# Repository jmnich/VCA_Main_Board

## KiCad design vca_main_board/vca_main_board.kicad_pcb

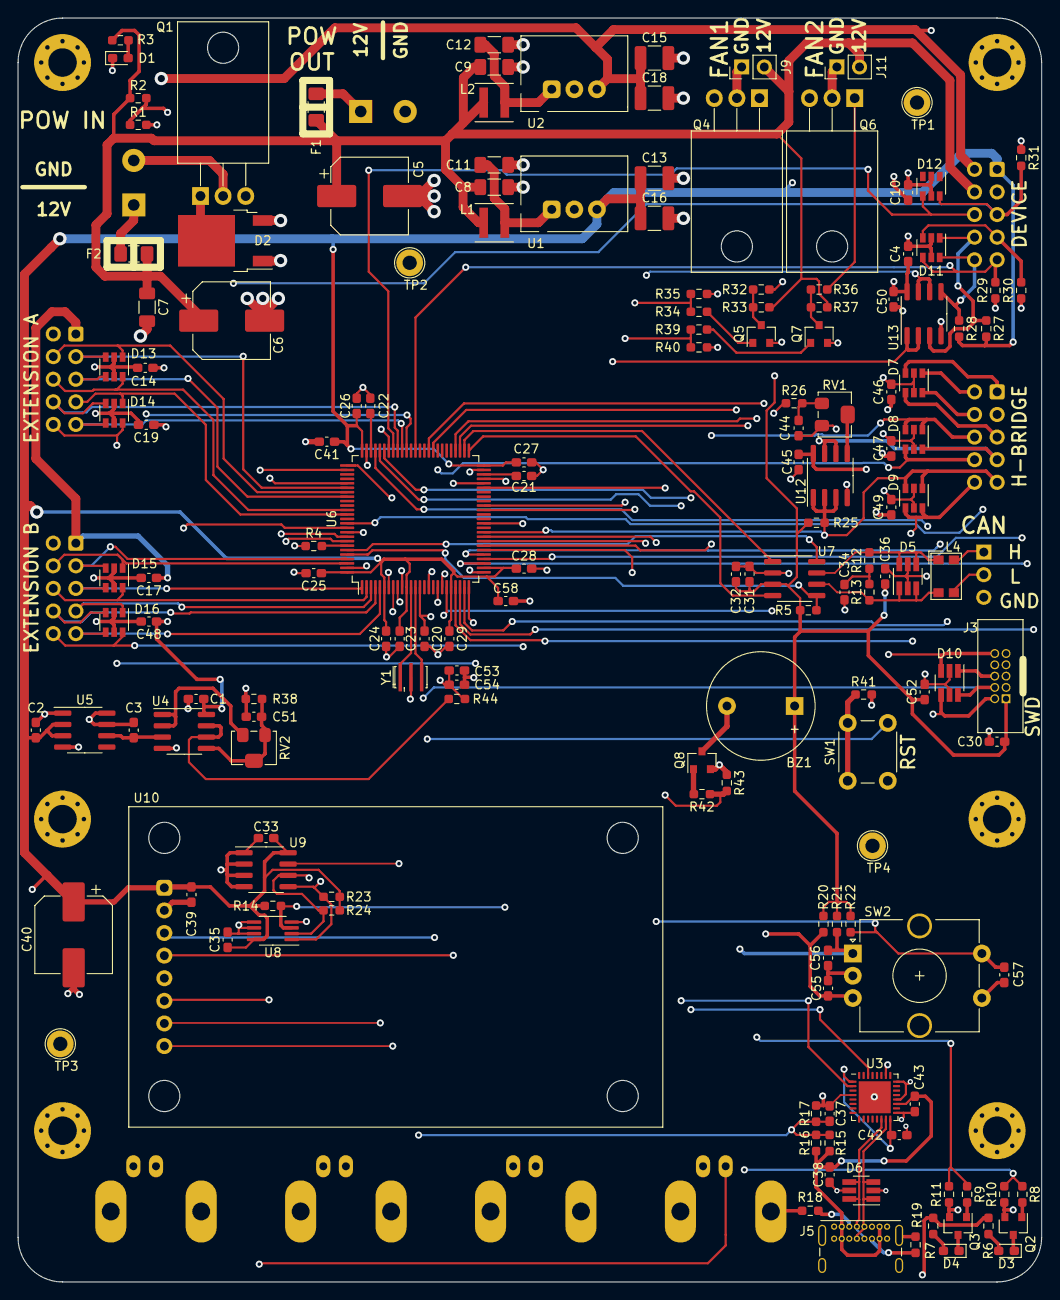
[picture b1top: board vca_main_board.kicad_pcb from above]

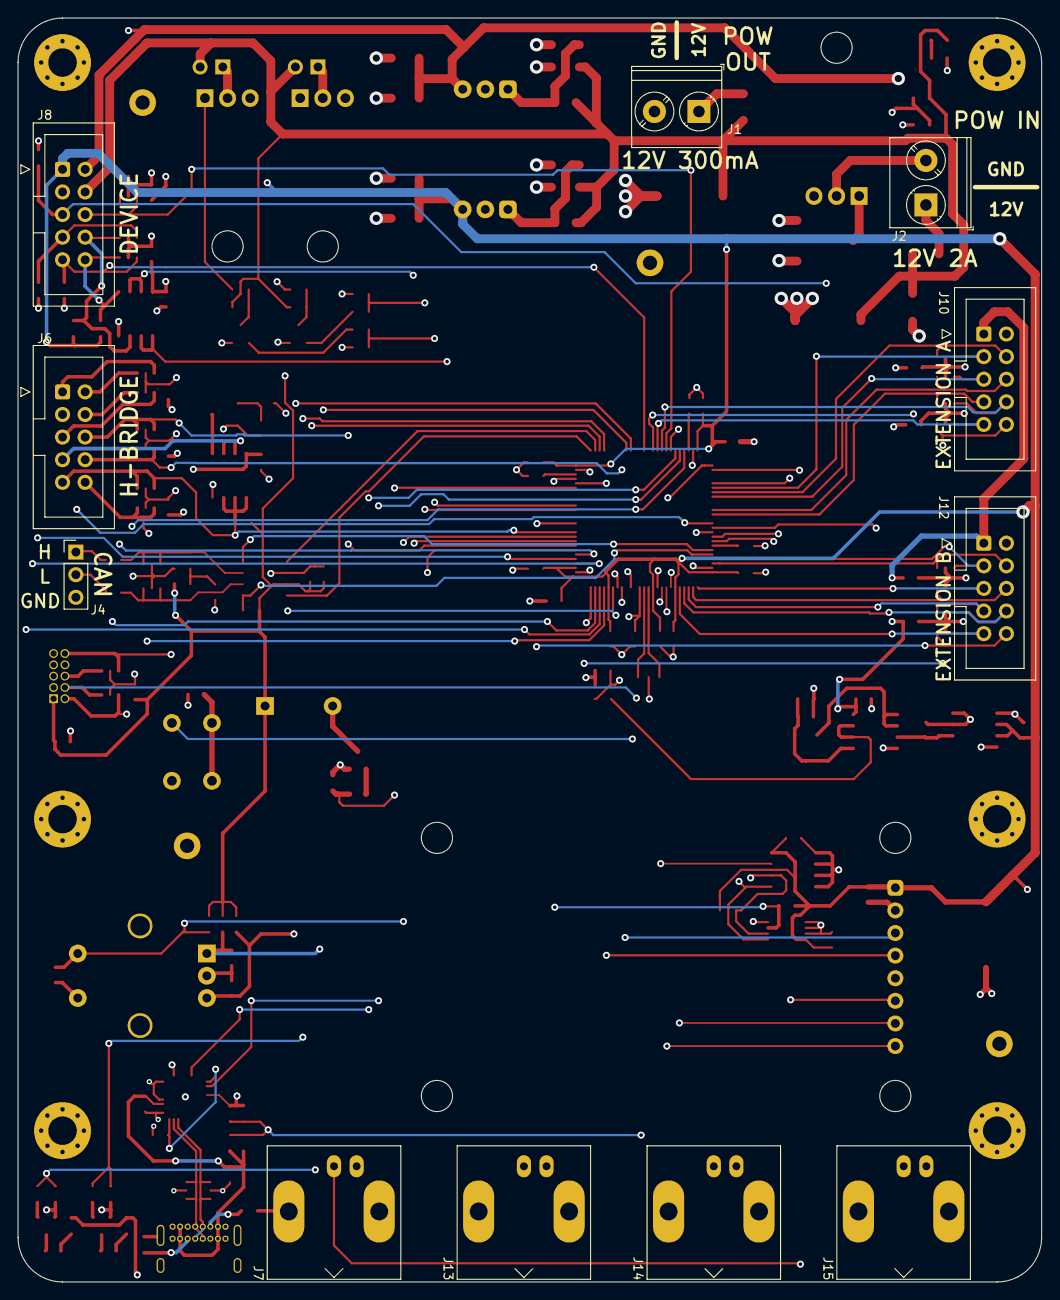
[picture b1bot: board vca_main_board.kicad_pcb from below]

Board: 4 copper layers, 115.0 x 142.0 mm, 174 parts (11 on the bottom side), 115 nets.

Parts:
BZ1: Buzzer; Buzzer_12x9.5RM7.6
C1: 1u 10V; C_0603_1608Metric_Pad1.08x0.95mm_HandSolder
C2, C3, C30, C32, C36, C39, C42, C43, C53: 1u 6.3V; C_0603_1608Metric_Pad1.08x0.95mm_HandSolder
C4, C10, C14, C17, C19, C37, C45, C46, C47, C48, C49, C50: 100n 10V; C_0603_1608Metric_Pad1.08x0.95mm_HandSolder
C5, C6, C40: 180u 50V; CP_Elec_8x10.5
C7, C8, C9, C11, C12: 10u 20V; C_1206_3216Metric_Pad1.33x1.80mm_HandSolder
C13, C15, C16, C18: 22u 10V; C_1210_3225Metric_Pad1.33x2.70mm_HandSolder
C20, C23, C24, C25, C26, C27, C28, C29, C31, C33, C35, C38, C44, C51, C52, C54, C55, C56, C57: 100n 6.3V; C_0603_1608Metric_Pad1.08x0.95mm_HandSolder
C21, C22: 2u2 6.3V; C_0603_1608Metric_Pad1.08x0.95mm_HandSolder
C34: 4n7 10V; C_0603_1608Metric_Pad1.08x0.95mm_HandSolder
C41, C58: 4.7u 6.3V; C_0603_1608Metric_Pad1.08x0.95mm_HandSolder
D1, D3, D4: LED GREEN; LED_0603_1608Metric_Pad1.05x0.95mm_HandSolder
D2: 10A 60V; TO-252-2
D5, D6, D10: ESDA6V1BC6; SOT-23-6_Handsoldering
D7, D8, D9, D11, D12, D13, D14, D15, D16: ESDA6V1BC6; SOT-23-6
F1: Fuse 500mA; Fuse_1206_3216Metric_Pad1.42x1.75mm_HandSolder
F2: Fuse 1A; Fuse_1206_3216Metric_Pad1.42x1.75mm_HandSolder
H1, H2, H3, H4, H5, H6: Hole; MountingHole_3.2mm_M3_Pad_Via
J1: 12V_OUT; TerminalBlock_Phoenix_PT-1,5-2-5.0-H_1x02_P5.00mm_Horizontal
J2: 12V_IN; TerminalBlock_Phoenix_PT-1,5-2-5.0-H_1x02_P5.00mm_Horizontal
J3: SWD; 10pin_1.27_socket
J4: CAN; PinHeader_1x03_P2.54mm_Vertical
J5: GCT USB4085; USB_C_Receptacle_GCT_USB4085
J6, J8, J10, J12: IDC10; IDC-Header_2x05_P2.54mm_Vertical
J7, J13, J14, J15: Conn_Coaxial; 1-1634613-0
J9: Extra_fan_1; PinHeader_1x02_P2.54mm_Vertical
J11: Extra_fan_2; PinHeader_1x02_P2.54mm_Vertical
L1, L2: XAL4030-472; L_Coilcraft_XxL4030
L4: PE-1812ACC101STS; L_CommonModeChoke_Coilcraft_1812CAN
Q1, Q4, Q6: IRF740; TO-220-3_Horizontal_TabDown
Q2, Q3, Q5, Q7, Q8: 2N7002; SOT-23
R1, R4, R10, R11, R14, R20, R21, R22, R29, R30, R31, R33, R35, R37, R40, R43: 47k 5%; R_0603_1608Metric_Pad0.98x0.95mm_HandSolder
R2: 100k 5%; R_0603_1608Metric_Pad0.98x0.95mm_HandSolder
R3, R38: 100k 1%; R_0603_1608Metric_Pad0.98x0.95mm_HandSolder
R5, R6, R7: 10k 5%; R_0603_1608Metric_Pad0.98x0.95mm_HandSolder
R8, R9, R32, R34, R36, R39, R41, R42: 1k 5%; R_0603_1608Metric_Pad0.98x0.95mm_HandSolder
R12, R13: 68R 1%; R_0603_1608Metric_Pad0.98x0.95mm_HandSolder
R15, R16, R17, R18, R19: 5k1 5%; R_0603_1608Metric_Pad0.98x0.95mm_HandSolder
R23, R24: 2k2 5%; R_0603_1608Metric_Pad0.98x0.95mm_HandSolder
R25, R27, R28: 10k 1%; R_0603_1608Metric_Pad0.98x0.95mm_HandSolder
R26: 5k1 1%; R_0603_1608Metric_Pad0.98x0.95mm_HandSolder
R44: 47R 1%; R_0603_1608Metric_Pad0.98x0.95mm_HandSolder
RV1, RV2: 10k; Bourns_3214W
SW1: RST; SW_PUSH_6mm_H4.3mm
SW2: ALPS_EC12E; RotaryEncoder_Alps_EC12E-Switch_Vertical_H20mm_CircularMoun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
TP1, TP2, TP3, TP4: GND; TestPoint_Loop_D2.60mm_Drill1.6mm_Beaded
U1: 173010335; 17301xx35
U2: 173010535; 17301xx35
U3: FT232RQ; QFN-32-1EP_5x5mm_P0.5mm_EP3.6x3.6mm
U4, U12, U13: ADA4522-2ARZ; SOIC-8_3.9x4.9mm_P1.27mm
U5: LM4140ACM-2.0; SOIC-8_3.9x4.9mm_P1.27mm
U6: STM32H743VITx; LQFP-100_14x14mm_P0.5mm
U7: TCAN337; SOIC-8_3.9x4.9mm_P1.27mm
U8: MCP9808_MSOP; MSOP-8_3x3mm_P0.65mm
U9: M24256-BR; SOIC-8_3.9x4.9mm_P1.27mm
U10: Waveshare_LCD_1_8; Waveshare_LCD_1.8
Y1: 10MHz; Resonator_SMD_muRata_CSTxExxV-3Pin_3.0x1.1mm_HandSoldering

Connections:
+3V3: BZ1.1, C2.1, C13.1, C16.1, C23.1, C24.1, C25.1, C26.1, C27.1, C28.1, C29.1, C30.1, C31.1, C32.1, C33.1, C35.1, C36.1, C39.1, C40.1, C41.1, C52.1, C58.1, J3.1, J8.1, R5.2, R6.2, R7.2, R14.2, R20.2, R21.2, R22.2, R23.2, R24.2, R25.2, R27.2, R28.2, U1.3, U5.2, U5.3, U6.6, U6.11, U6.21, U6.27, U6.50, U6.75, U6.100, U7.3, U8.8, U9.8, U10.1
+5V: C1.1, C4.1, C10.1, C14.1, C15.1, C17.1, C18.1, C19.1, C45.1, C46.1, C47.1, C48.1, C49.1, C50.1, J8.2, J10.1, J12.1, U2.3, U4.8, U12.8, U13.8
+12V: C5.1, C6.1, C7.1, C8.1, C9.1, F1.1, F2.1, J8.4, J9.2, J11.2, L1.1, L2.1, R2.1, R3.1, R33.2, R37.2
/Coil_Fans: D12.4, J8.6, U6.68
/Coil_Thermistor_1: U6.31, U13.1, U13.2
/Coil_Thermistor_2: U6.33, U13.6, U13.7
/Device connenction/THERMISTOR_1: D11.1, J8.8, R27.1, U13.3
/Device connenction/THERMISTOR_2: D11.6, J8.10, R28.1, U13.5
/EXTA_0: D13.3, J10.3, U6.81
/EXTA_1: D13.1, J10.4, U6.82
/EXTA_2: D13.4, J10.5, U6.83
/EXTA_3: D13.6, J10.6, U6.86
/EXTA_4: D14.1, J10.7, U6.87
/EXTA_5: D14.3, J10.8, U6.67
/EXTA_6: D14.4, J10.9, U6.66
/EXTA_7: D14.6, J10.10, U6.25
/EXTB_0: D15.3, J12.3, U6.97
/EXTB_1: D15.1, J12.4, U6.98
/EXTB_2: D15.4, J12.5, U6.1
/EXTB_3: D15.6, J12.6, U6.2
/EXTB_4: D16.1, J12.7, U6.3
/EXTB_5: D16.3, J12.8, U6.4
/EXTB_6: D16.4, J12.9, U6.5
/EXTB_7: D16.6, J12.10, U6.37
/FAN_1: R34.1, R35.2, U6.40
/FAN_2: R39.1, R40.2, U6.41
/GPIO_A: J14.1, U6.91
/GPIO_B: J15.1, U6.65
/H bridge connection/REF_IN: D8.6, J6.7, U12.6, U12.7
/H_Current: D8.4, J6.8, U6.18
/H_Excitation: D7.3, J6.1, U6.28
/H_Load_Volt: D7.1, J6.2, U6.30
/H_Offset: D7.4, J6.5, U6.29
/H_Ref_High: D7.6, J6.4, U6.24
/H_Sum: D8.1, D8.3, J6.6, U6.32
/H_Thermistor: D9.1, D9.3, J6.9, R25.1, U6.35, U12.1, U12.2, U12.3
/H_Voltage: D9.4, D9.6, J6.10, U6.22
/MCU/BOOT0: R4.2, U6.94
/MCU/BUZZ: R42.1, R43.2, U6.45
/MCU/CAN_FAULT: R5.1, U6.96, U7.5
/MCU/CAN_S: U6.95, U7.8
/MCU/EEP_~WC: U6.9, U9.7
/MCU/FDCAN_RX: U6.51, U7.4
/MCU/FDCAN_TX: U6.52, U7.1
/MCU/Knob_A: C56.2, R21.1, SW2.A, U6.59
/MCU/Knob_B: C55.2, R20.1, SW2.B, U6.60
/MCU/Knob_S: C57.2, R22.1, SW2.S1, U6.34
/MCU/LCD_BL: U6.8, U10.8
/MCU/LCD_CLK: U6.46, U10.4
/MCU/LCD_CS: U6.90, U10.5
/MCU/LCD_DC: U6.80, U10.6
/MCU/LCD_DIN: U6.16, U10.3
/MCU/LCD_RST: U6.7, U10.7
/MCU/LED_1: R8.1, R10.2, U6.53
/MCU/LED_2: R9.1, R11.2, U6.54
/MCU/NRST: C20.1, D10.3, J3.10, SW1.2, U6.14
/MCU/SCL: R24.1, U6.92, U8.2, U9.6
/MCU/SDA: R23.1, U6.93, U8.1, U9.5
/MCU/SWDCLK: D10.6, J3.4, U6.76
/MCU/SWDIO: D10.4, J3.2, U6.72
/MCU/SWO: D10.1, J3.6, U6.89
/MCU/TH_ALERT: R14.1, U6.47, U8.3
/MCU/USB_DET: C37.1, R15.2, R16.2, R17.1, U6.69
/MCU/USB_RX: U3.2, U6.71
/MCU/USB_TX: U3.30, U6.70
/MCU/peripherals/DM: D6.1, D6.3, J5.A7, J5.B7, U3.15
/MCU/peripherals/DP: D6.4, D6.6, J5.A6, J5.B6, U3.14
/Mirror_Enc_A: D12.6, J7.1, J8.5, R31.2, U6.77
/Mirror_Enc_B: D11.3, J8.7, J13.1, R30.2, U6.23
/Mirror_Enc_Z: D11.4, J8.9, R29.2, U6.63
/VREF: C53.1, C54.1, R26.1, R44.2, U6.20
GND: C1.2, C2.2, C3.2, C4.2, C5.2, C6.2, C7.2, C8.2, C9.2, C10.2, C11.2, C12.2, C13.2, C14.2, C15.2, C16.2, C17.2, C18.2, C19.2, C20.2, C21.2, C22.2, C23.2, C24.2, C25.2, C26.2, C27.2, C28.2, C29.2, C30.2, C31.2, C32.2, C33.2, C34.2, C35.2, C36.2, C37.2, C38.2, C39.2, C40.2, C41.2, C42.2, C43.2, C44.2, C45.2, C46.2, C47.2, C48.2, C49.2, C50.2, C51.2, C52.2, C53.2, C54.2, C55.1, C56.1, C57.1, C58.2, D1.1, D2.1, D2.3, D5.2, D5.5, D6.2, D6.5, D7.2, D7.5, D8.2, D8.5, D9.2, D9.5, D10.2, D10.5, D11.2, D11.5, D12.2, D12.5, D13.2, D13.5, D14.2, D14.5, D15.2, D15.5, D16.2, D16.5, J1.2, J3.3, J3.5, J3.9, J4.3, J5.A1, J5.A12, J5.B1, J5.B12, J5.S1, J6.3, J7.2, J8.3, J10.2, J12.2, J13.2, J14.2, J15.2, Q1.3, Q2.2, Q3.2, Q4.3, Q5.2, Q6.3, Q7.2, Q8.2, R1.2, R4.1, R10.1, R11.1, R17.2, R18.2, R19.2, R29.1, R30.1, R31.1, R35.1, R38.1, R40.1, R41.2, R43.1, RV1.3, SW2.C, SW2.S2, TP1.1, TP2.1, TP3.1, TP4.1, U1.2, U2.2, U3.4, U3.17, U3.20, U3.24, U3.26, U4.4, U5.1, U5.4, U5.7, U5.8, U6.10, U6.19, U6.26, U6.49, U6.74, U6.99, U7.2, U8.4, U8.5, U8.6, U8.7, U9.1, U9.2, U9.3, U9.4, U10.2, U12.4, U13.4, Y1.2
unnamed: BZ1.2, Q8.3
unnamed: C3.1, U4.3, U5.6
unnamed: C11.1, L1.2, U1.1
unnamed: C12.1, L2.2, U2.1
unnamed: C21.1, U6.48
unnamed: C22.1, U6.73
unnamed: C34.1, R12.1, R13.2
unnamed: C42.1, U3.1, U3.16
unnamed: C44.1, R26.2, RV1.1
unnamed: C51.1, R38.2, RV2.1, RV2.2, U4.5
unnamed: D1.2, R3.2
unnamed: D2.2, Q1.1, R1.1, R2.2
unnamed: D3.1, Q2.3
unnamed: D3.2, R6.1
unnamed: D4.1, Q3.3
unnamed: D4.2, R7.1
unnamed: D5.1, D5.3, L4.2, R13.1, U7.6
unnamed: D5.4, D5.6, L4.1, R12.2, U7.7
unnamed: F1.2, J1.1
unnamed: F2.2, J2.1
unnamed: J2.2, Q1.2
unnamed: J4.1, L4.4
unnamed: J4.2, L4.3
unnamed: J5.A5, R18.1
unnamed: J5.B5, R19.1
unnamed: J9.1, Q4.2
unnamed: J11.1, Q6.2
unnamed: Q2.1, R8.2
unnamed: Q3.1, R9.2
unnamed: Q4.1, R32.2
unnamed: Q5.1, R34.2
unnamed: Q5.3, R32.1, R33.1
unnamed: Q6.1, R36.2
unnamed: Q7.1, R39.2
unnamed: Q7.3, R36.1, R37.1
unnamed: Q8.1, R42.2
unnamed: R41.1, SW1.1
unnamed: R44.1, U4.6, U4.7
unnamed: RV1.2, U12.5
unnamed: RV2.3, U4.1, U4.2
unnamed: U6.12, Y1.1
unnamed: U6.13, Y1.3
VBUS: C38.1, C43.1, J5.A4, J5.A9, J5.B4, J5.B9, R15.1, R16.1, U3.19

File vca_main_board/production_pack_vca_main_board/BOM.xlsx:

Value | Reference | Footprint | LCSC Part Number
1u 10V | C1 | Capacitor_SMD:C_0603_1608Metric_Pad1.08x0.95mm_HandSolder | C83059
22u 10V | C13,C15,C16,C18 | Capacitor_SMD:C_1210_3225Metric_Pad1.33x2.70mm_HandSolder | C109447
100n 10V | C4,C10,C14,C17,C19,C37,C45,C46,C47,C48,C49,C50 | Capacitor_SMD:C_0603_1608Metric_Pad1.08x0.95mm_HandSolder | C519438
2u2 6.3V | C21,C22 | Capacitor_SMD:C_0603_1608Metric_Pad1.08x0.95mm_HandSolder | C100082
1u 6.3V | C2,C3,C30,C32,C36,C39,C42,C43,C53 | Capacitor_SMD:C_0603_1608Metric_Pad1.08x0.95mm_HandSolder | C83059
4n7 10V | C34 | Capacitor_SMD:C_0603_1608Metric_Pad1.08x0.95mm_HandSolder | C53987
4.7u 6.3V | C41,C58 | Capacitor_SMD:C_0603_1608Metric_Pad1.08x0.95mm_HandSolder | C69335
100n 6.3V | C20,C23,C24,C25,C26,C27,C28,C29,C31,C33,C35,C38,C44,C51,C52,C54,C55,C56,C57 | Capacitor_SMD:C_0603_1608Metric_Pad1.08x0.95mm_HandSolder | C519438
10u 20V | C7,C8,C9,C11,C12 | Capacitor_SMD:C_1206_3216Metric_Pad1.33x1.80mm_HandSolder | C14860
LED GREEN | D1,D3,D4 | LED_SMD:LED_0603_1608Metric_Pad1.05x0.95mm_HandSolder | C205450
ESDA6V1BC6 | D7,D8,D9,D11,D12,D13,D14,D15,D16,D5,D6,D10 | Package_TO_SOT_SMD:SOT-23-6 | C283620
Fuse 500mA | F1 | Fuse:Fuse_1206_3216Metric_Pad1.42x1.75mm_HandSolder | C377237
Fuse 1A | F2 | Fuse:Fuse_1206_3216Metric_Pad1.42x1.75mm_HandSolder | C377288
IRF740 | Q1,Q4,Q6 | Package_TO_SOT_THT:TO-220-3_Horizontal_TabDown | C358408
2N7002 | Q2,Q3,Q5,Q7,Q8 | Package_TO_SOT_SMD:SOT-23 | C2836920
68R 1% | R12,R13 | Resistor_SMD:R_0603_1608Metric_Pad0.98x0.95mm_HandSolder | C126362
5k1 1% | R15,R16,R17,R18,R19,R26 | Resistor_SMD:R_0603_1608Metric_Pad0.98x0.95mm_HandSolder | C105580
2k2 5% | R23,R24 | Resistor_SMD:R_0603_1608Metric_Pad0.98x0.95mm_HandSolder | C427273
10k 1% | R5,R6,R7,R25,R27,R28 | Resistor_SMD:R_0603_1608Metric_Pad0.98x0.95mm_HandSolder | C98220
1k 5% | R8,R9,R32,R34,R36,R39,R41,R42 | Resistor_SMD:R_0603_1608Metric_Pad0.98x0.95mm_HandSolder | C269704
47k 5% | R1,R4,R10,R11,R14,R20,R21,R22,R29,R30,R31,R33,R35,R37,R40,R43 | Resistor_SMD:R_0603_1608Metric_Pad0.98x0.95mm_HandSolder | C136590
100k 1% | R2,R3,R38 | Resistor_SMD:R_0603_1608Metric_Pad0.98x0.95mm_HandSolder | C14675
47R 1% | R44 | Resistor_SMD:R_0603_1608Metric_Pad0.98x0.95mm_HandSolder | C114623
M24256-BR | U9 | Package_SO:SOIC-8_3.9x4.9mm_P1.27mm | C79984

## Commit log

2021-10-29 Schematic in progress
2022-01-17 done
